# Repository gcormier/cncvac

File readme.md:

# cncvac

This is a 433MHz ASK/FSK transmitter controlled by an ATTINY841.

It runs off regular AA/AAA batteries and can be used to control various devices like garage doors, gates, etc. The intent was to have it control my dust collection system in the shop which is using the iVac Pro system. The iVac Pro system is a great system but it is expensive and I wanted to have a cheaper alternative to control it, and the company did not offer a remote control that could be triggered from a logic signal. (They now sell one)

It has an opto-isolated input controlled by a 5-24V logic signal.

### Case
This fits in a [Hammond 1593P case](https://www.digikey.ca/en/products/detail/hammond-manufacturing/1593PBK/270098) and can use their [battery holder](https://www.digikey.ca/en/products/detail/hammond-manufacturing/BH3AAAW/3869833) as well.

### Power Consumption
#### Transmitting
1mV = 1uA
1-3mA while transmitting

#### Sleep/Idle
1mV = 1nA
Better than 1.2uA while sleeping
Based on the average capacity of two AA NiMH batteries, 2000mAh, this should last almost 200 years.

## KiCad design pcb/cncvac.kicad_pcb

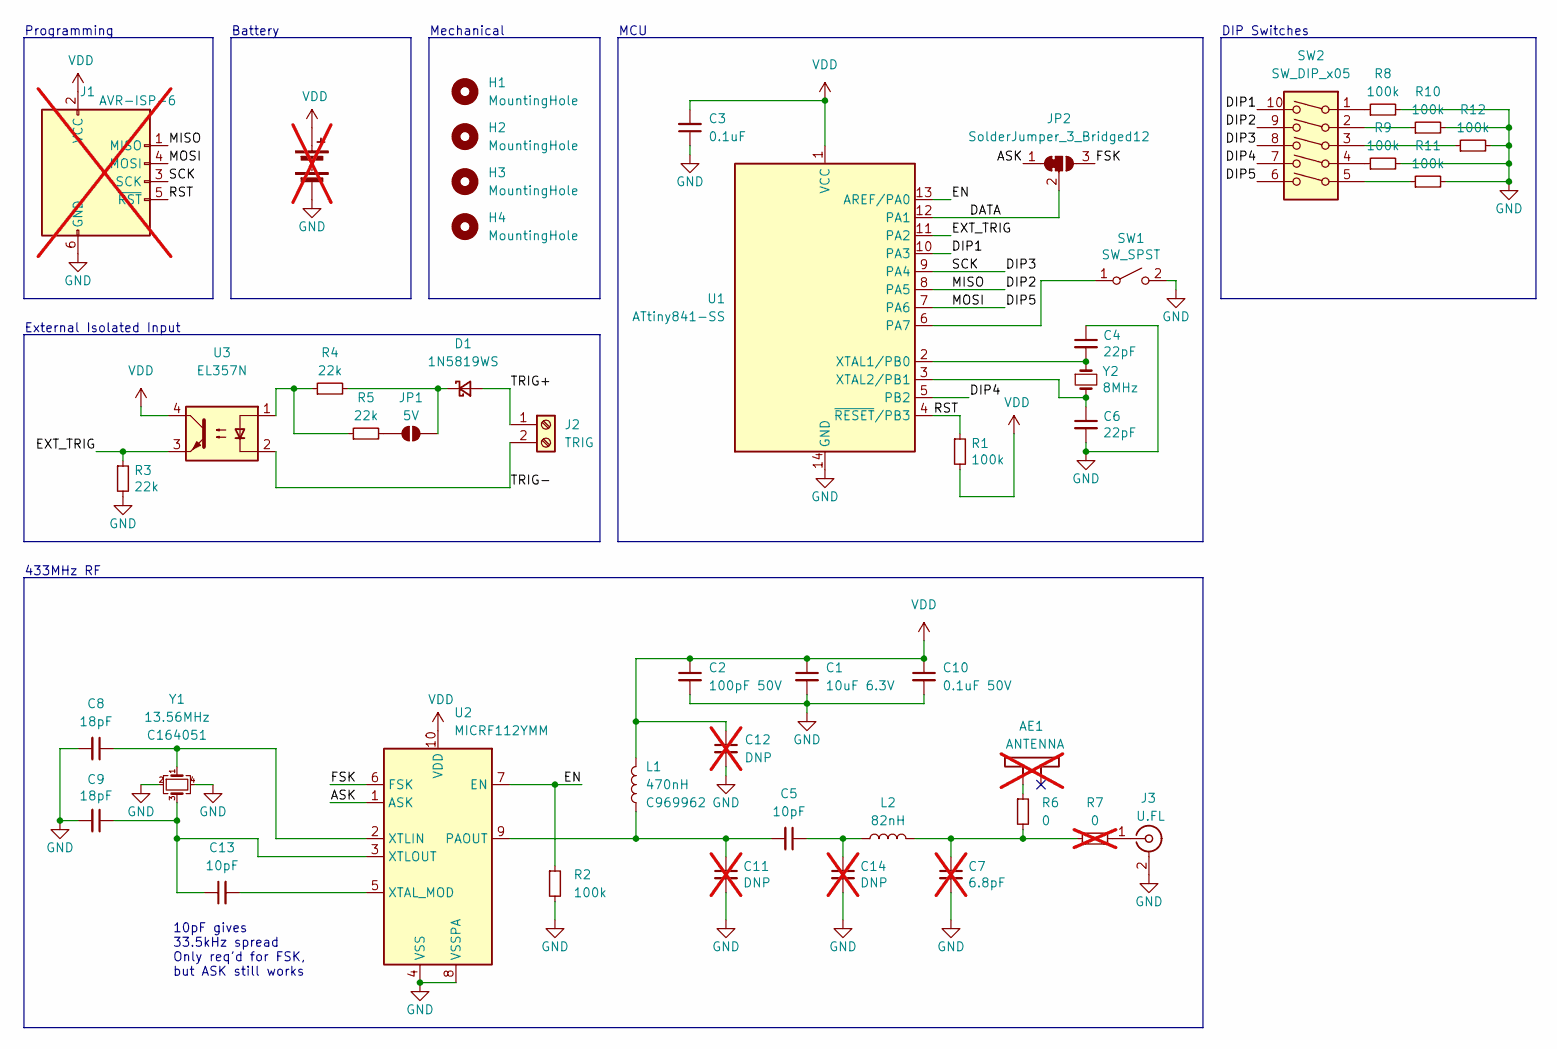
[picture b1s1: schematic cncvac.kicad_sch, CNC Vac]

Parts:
AE1: ANTENNA; ANT-433-HETH; not fitted
BT1: Battery; PinHeader_1x02_P2.54mm_Vertical; not fitted
C1: 10uF 6.3V; C_0402_1005Metric; LCSC C15525
C2: 100pF 50V; C_0402_1005Metric; LCSC C1546
C3: 0.1uF; C_0402_1005Metric; LCSC C307331
C4, C6: 22pF; C_0402_1005Metric; LCSC C1555
C5, C13: 10pF; C_0402_1005Metric; LCSC C32949
C7: 6.8pF; C_0402_1005Metric; not fitted
C8, C9: 18pF; C_0402_1005Metric; LCSC C1549
C10: 0.1uF 50V; C_0402_1005Metric; LCSC C307331
C11, C12, C14: DNP; C_0402_1005Metric; not fitted
D1: 1N5819WS; D_SOD-323; LCSC C191023
H1, H2, H3, H4: MountingHole; MountingHole_3.2mm_M3
J1: AVR-ISP-6; IDC-Header_2x03_P2.54mm_Vertical; not fitted
J2: TRIG; PhoenixContact_MC_1,5_2-G-3.81_1x02_P3.81mm_Horizontal; LCSC C8387
J3: U.FL; U.FL_Hirose_U.FL-R-SMT-1_Vertical; LCSC C5137195
JP1: 5V; SolderJumper-2_P1.3mm_Open_RoundedPad1.0x1.5mm
JP2: SolderJumper_3_Bridged12; SolderJumper-3_P1.3mm_Bridged12_RoundedPad1.0x1.5mm_NumberL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
L1: 470nH; L_0402_1005Metric; LCSC C969962
L2: 82nH; L_0402_1005Metric; LCSC C275301
R1, R2, R8, R9, R10, R11, R12: 100k; R_0402_1005Metric; LCSC C25741
R3, R4, R5: 22k; R_0805_2012Metric; LCSC C17560
R6: 0; R_0402_1005Metric; LCSC C17168
R7: 0; R_0402_1005Metric; LCSC C17168; not fitted
SW1: SW_SPST; SW_Push_1P1T_XKB_TS-1187A; LCSC C318884
SW2: SW_DIP_x05; SW_DIP_SPSTx05_Slide_9.78x14.88mm_W7.62mm_P2.54mm; LCSC C129061
U1: ATtiny841-SS; SOIC-14_3.9x8.7mm_P1.27mm; LCSC C614879
U2: MICRF112YMM; MSOP-10_3x3mm_P0.5mm; LCSC C481379
U3: EL357N; SO-4_4.4x3.6mm_P2.54mm; LCSC C42381015
Y1: 13.56MHz; Crystal_SMD_3225-4Pin_3.2x2.5mm; LCSC C164051
Y2: 8MHz; Crystal_SMD_5032-2Pin_5.0x3.2mm; LCSC C115962

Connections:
/ASK: JP2.1 (A), U2.1 (ASK)
/DATA: JP2.2 (C), U1.12 (PA1)
/DIP1: SW2.10, U1.10 (PA3)
/DIP2: J1.1 (MISO), SW2.9, U1.8 (PA5)
/DIP3: J1.3 (SCK), SW2.8, U1.9 (PA4)
/DIP4: SW2.7, U1.5 (PB2)
/DIP5: J1.4 (MOSI), SW2.6, U1.7 (PA6)
/EN: R2.1, U1.13 (AREF/PA0), U2.7 (EN)
/EXT_TRIG: R3.1, U1.11 (PA2), U3.3
/FSK: JP2.3 (B), U2.6 (FSK)
/RST: J1.5 (~RST), R1.1, U1.4 (~RESET/PB3)
/TRIG+: D1.2 (A), J2.1
/TRIG-: J2.2, U3.2
GND: BT1.2 (-), C1.2, C2.2, C3.1, C4.1, C6.2, C7.2, C8.2, C9.2, C10.2, C11.2, C12.2, C14.2, J1.6 (GND), J3.2 (Ext), R2.2, R3.2, R8.2, R9.2, R10.2, R11.2, R12.2, SW1.2 (B), U1.14 (GND), U2.4 (VSS), U2.8 (VSSPA), Y1.2, Y1.4
unnamed: AE1.2, R6.1
unnamed: C7.1, L2.2, R6.2, R7.1
unnamed: C5.1, C14.1, L2.1
unnamed: D1.1 (K), JP1.2 (B), R4.2
unnamed: J3.1 (In), R7.2
unnamed: JP1.1 (A), R5.2
unnamed: R4.1, R5.1, U3.1
unnamed: R8.1, SW2.1
unnamed: R9.1, SW2.4
unnamed: R10.1, SW2.2
unnamed: R11.1, SW2.5
unnamed: R12.1, SW2.3
unnamed: SW1.1 (A), U1.6 (PA7)
unnamed: C4.2, U1.2 (XTAL1/PB0), Y2.1
unnamed: C6.1, U1.3 (XTAL2/PB1), Y2.2
unnamed: C5.2, C11.1, L1.1, U2.9 (PAOUT)
unnamed: C13.2, U2.5 (XTAL_MOD)
unnamed: C8.1, U2.2 (XTLIN), Y1.1
unnamed: C9.1, C13.1, U2.3 (XTLOUT), Y1.3
VDD: BT1.1 (+), C1.1, C2.1, C3.2, C10.1, C12.1, J1.2 (VCC), L1.2, R1.2, U1.1 (VCC), U2.10 (VDD), U3.4

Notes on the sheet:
MCU
10pF gives 33.5kHz spread Only req'd for FSK, but ASK still works
Mechanical
External Isolated Input
Programming
Battery
433MHz RF
DIP Switches

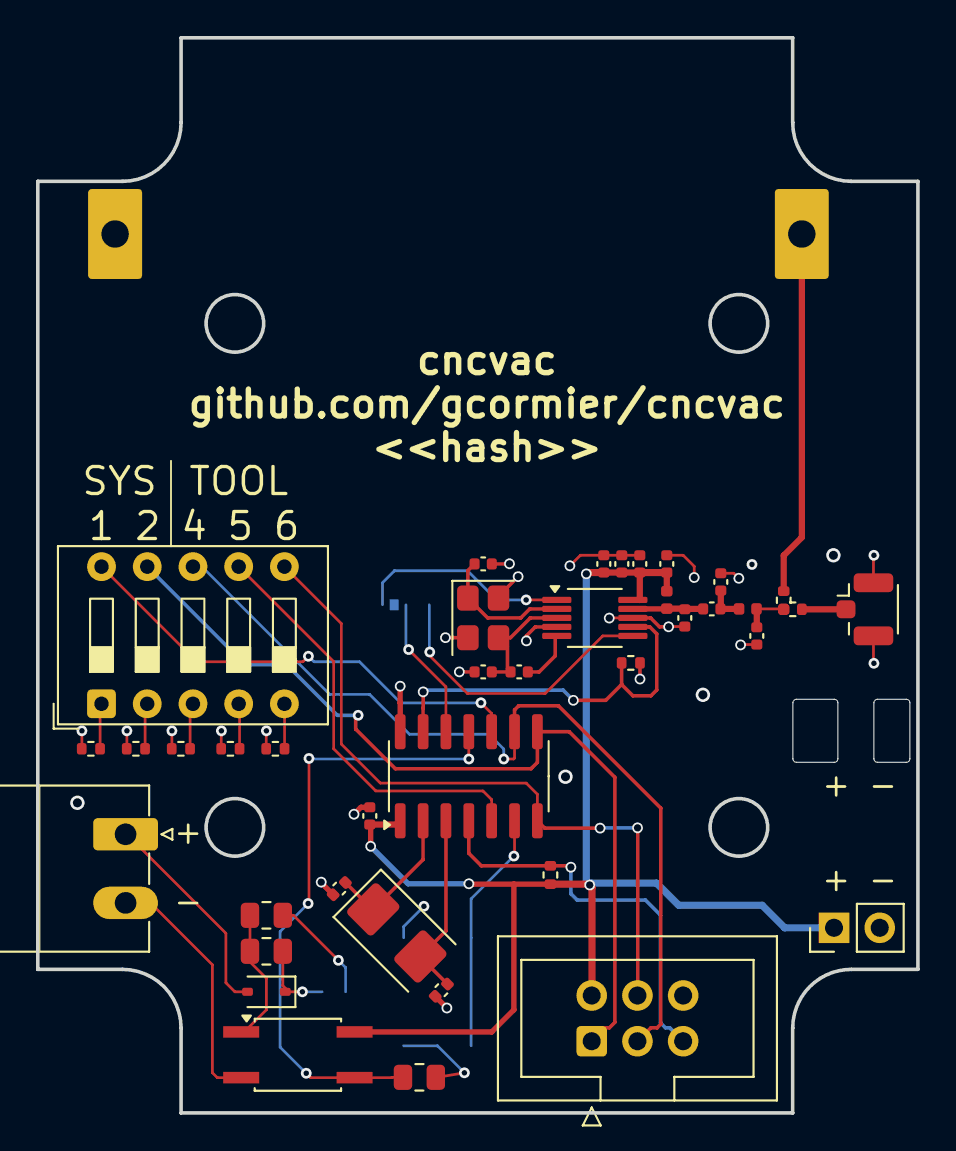
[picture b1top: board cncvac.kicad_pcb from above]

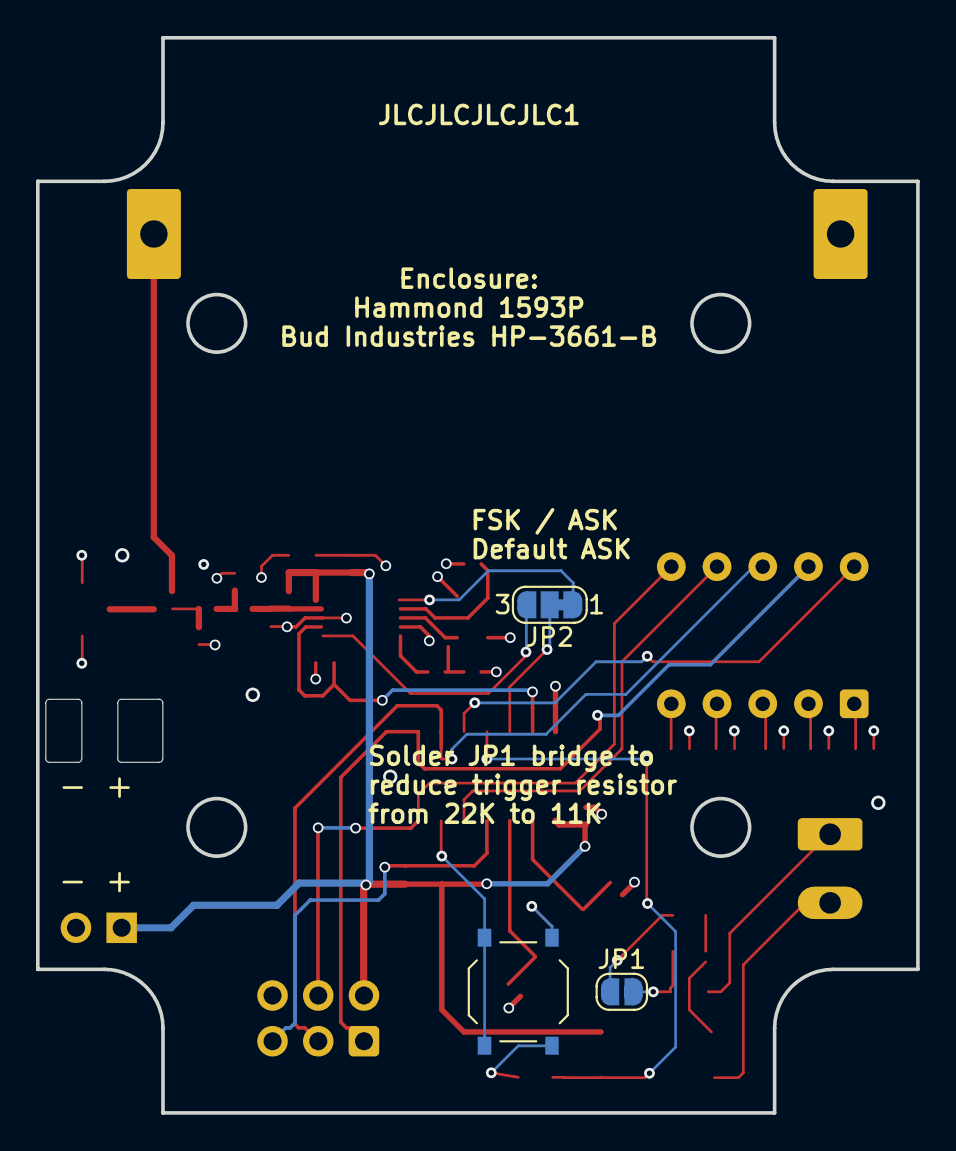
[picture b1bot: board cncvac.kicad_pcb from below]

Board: 4 copper layers, 48.9 x 59.7 mm, 47 parts (3 on the bottom side), 34 nets.

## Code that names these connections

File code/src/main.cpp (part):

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
///// Pinout https://github.com/SpenceKonde/ATTinyCore/blob/v2.0.0-devThis-is-the-head-submit-PRs-against-this/avr/extras/Pinout_x41.jpg
// Misery.
// PA0 or PORTA0 is defined by shitty platformio Atmel libraries and is broken
// A8 is defined by tinyavr and uses the clockwise/counterclockwise mapping. but it seems to break after a bit.
// Use raw numbers and test each output to make sure it works.

#define PIN_EN 0        // PA0, Pin 13, Arduino 10
#define PIN_DATA 1      // PA1, Pin 11, Arduino 8
#define PIN_BUTTON 7    // PA7, Pin 6, PCINT7
#define PIN_EXT_TRIG 2


// DIP switch pins for configuration
#define PIN_DIP1 3    // PA3 - SYS bit 1
#define PIN_DIP2 5    // PA5 - SYS bit 0
#define PIN_DIP3 4    // PA4 - TOOL bit 2
#define PIN_DIP4 8    // PB2 - TOOL bit 1
#define PIN_DIP5 6    // PA6 - TOOL bit 0


#define ENHIGH (bitSet(PORTA, PIN_EN))
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{
  // Read DIP switch settings
  // DIP switches are active HIGH (pulled low by default, connected to VCC when ON)
  uint8_t sys0 = !digitalRead(PIN_DIP1);   // PA3 - DIP1 is SYS bit 0 (lower bit)
  uint8_t sys1 = !digitalRead(PIN_DIP2);   // PA5 - DIP2 is SYS bit 1 (upper bit)
  uint8_t tool0 = !digitalRead(PIN_DIP3);  // PA4 - DIP3 is TOOL bit 0 (lower bit)
  uint8_t tool1 = !digitalRead(PIN_DIP4);  // PB2 - DIP4 is TOOL bit 1 (middle bit)
  uint8_t tool2 = !digitalRead(PIN_DIP5);  // PA6 - DIP5 is TOOL bit 2 (upper bit)
  
  // Build the base packet with FIXED preamble
  unsigned short basePacket = FIXED;
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  PCMSK0 |= (1 << PIN_BUTTON);

  // Opto interrupt
  PCMSK0 |= (1 << PIN_EXT_TRIG);
  GIMSK |= (1 << PCIE0);

  interrupts();
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  // button interrupt
  PCMSK0 |= (1 << PIN_BUTTON);
  // Opto interrupt
  PCMSK0 |= (1 << PIN_EXT_TRIG);
  GIMSK |= (1 << PCIE0);

  interrupts();
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  // button interrupt
  PCMSK0 |= (1 << PIN_BUTTON);
  // Opto interrupt
  PCMSK0 |= (1 << PIN_EXT_TRIG);
  GIMSK |= (1 << PCIE0);

  interrupts();
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  pinMode(PIN_EN, OUTPUT);
  pinMode(PIN_DATA, OUTPUT);
  pinMode(PIN_BUTTON, INPUT_PULLUP);
  pinMode(PIN_EXT_TRIG, INPUT);
  
  // Configure DIP switch pins as inputs
  pinMode(PIN_DIP1, INPUT_PULLUP);
  pinMode(PIN_DIP2, INPUT_PULLUP);
  pinMode(PIN_DIP3, INPUT_PULLUP);
  pinMode(PIN_DIP4, INPUT_PULLUP);
  pinMode(PIN_DIP5, INPUT_PULLUP);

  // Read DIP switches and configure packets - only needs to be done once at startup
  // The AVR maintains state and ISRs will use the globally set packet values
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  // could use a +300ms debounce here, but its not critcal if we transmit packets twice...
  if (digitalRead(PIN_BUTTON) == LOW)
    wakeupReason = 1;
  else if (digitalRead(PIN_EXT_TRIG) == LOW)
  {
    //digitalWrite(PIN_MISC, LOW);
    wakeupReason = 2;
    currentPacket = offPacket;
  }
  else if (digitalRead(PIN_EXT_TRIG) == HIGH)
  {
    //digitalWrite(PIN_MISC, HIGH);
    wakeupReason = 2;
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
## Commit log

2025-01-01 del backujp
2025-01-01 givver
2025-01-01 automation
2025-01-01 ren2
2025-01-01 ren3
2025-01-01 ren4
2025-01-02 tweak
2025-01-02 pn's
2025-01-02 add via for rf test
2025-01-11 codecode
2025-01-11 moar
2025-01-11 rexmit and tune
2025-01-12 fixed width pwm
2025-01-12 opto
2025-01-13 shift the antenna opening in the panel slightly
2025-01-15 notes and render
2025-01-16 pin nightmare for interrupts
2025-01-16 victory is mine
2025-01-17 3dmouse
2025-01-17 mouse
2025-01-17 Add protection diode to opto, increase pulldown strength
2025-01-18 update code
2025-01-18 power
2025-06-15 fixup
2025-06-15 fix silk
2025-06-15 update part number for opto
2025-06-17 fix pn for opto
2025-10-26 initial dips
2025-10-26 probably fix portb pin
2025-10-26 business time
2025-10-26 working
